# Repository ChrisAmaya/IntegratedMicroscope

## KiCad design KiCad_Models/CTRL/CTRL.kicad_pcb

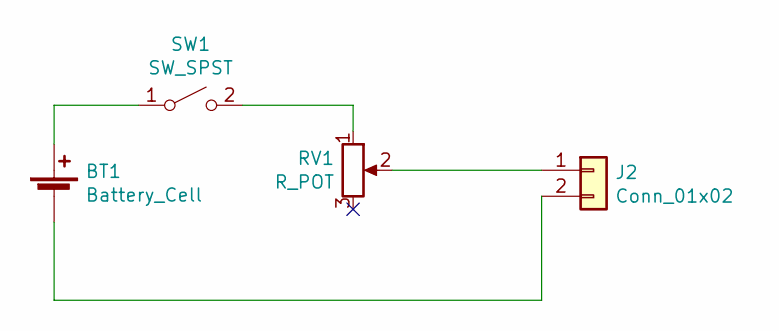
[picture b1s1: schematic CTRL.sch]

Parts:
BT1: Battery_Cell; BatteryHolder_Keystone_1058_1x2032
J2: Conn_01x02; Molex_PicoBlade_53047-0210_1x02_P1.25mm_Vertical
RV1: R_POT; Potentiometer_Bourns_PRS11S_Vertical
SW1: SW_SPST; SW_SPST_EVQPE1

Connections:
unnamed: BT1.1 (+), SW1.1 (A)
unnamed: BT1.2 (-), J2.2
unnamed: J2.1, RV1.2
unnamed: RV1.1, SW1.2 (B)

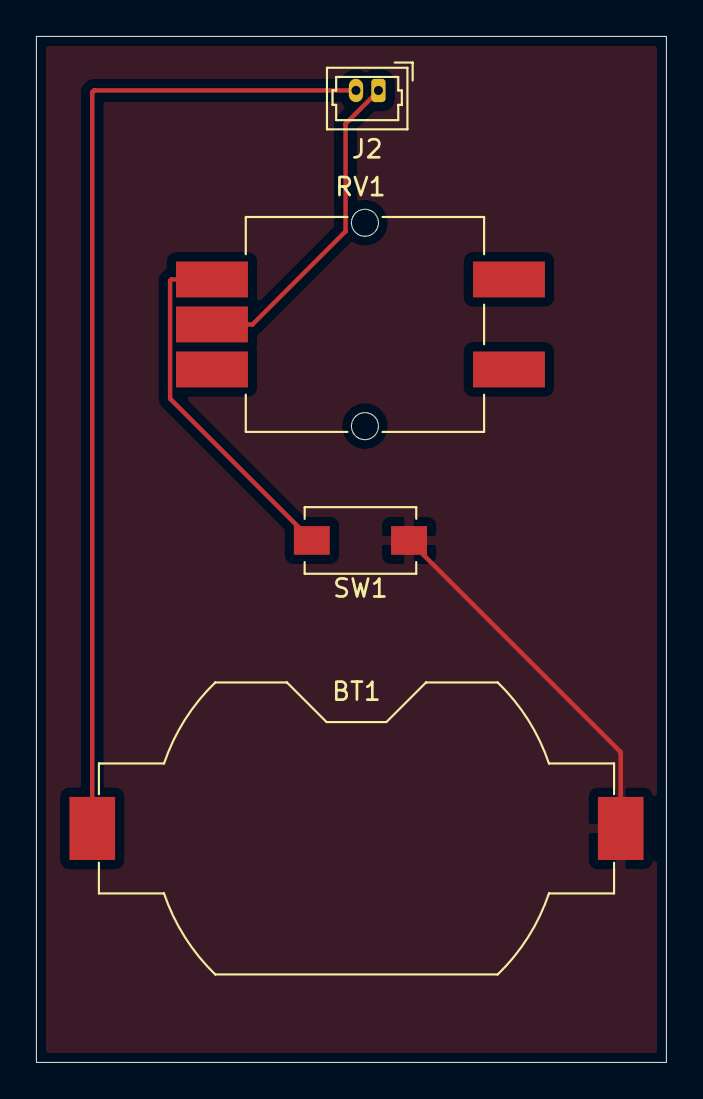
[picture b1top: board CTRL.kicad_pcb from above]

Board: 2 copper layers, 35.0 x 57.0 mm, 4 parts (0 on the bottom side), 4 nets.

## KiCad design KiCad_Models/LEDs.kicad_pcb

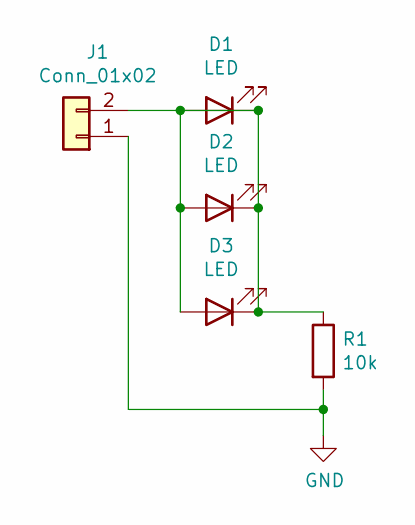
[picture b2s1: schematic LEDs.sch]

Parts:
D1, D2, D3: LED; LED_0805_2012Metric_Pad1.15x1.40mm_HandSolder
J1: Conn_01x02; Molex_PicoBlade_53047-0210_1x02_P1.25mm_Vertical
R1: 10k; R_0201_0603Metric

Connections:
GND: J1.1, R1.2
unnamed: D1.1 (K), D1.2 (A), D2.1 (K), D2.2 (A), D3.1 (K), D3.2 (A), J1.2, R1.1

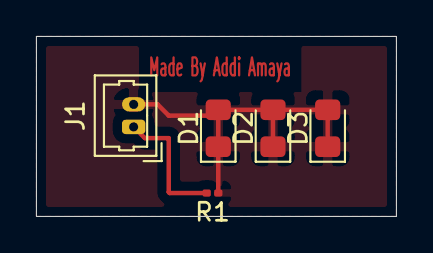
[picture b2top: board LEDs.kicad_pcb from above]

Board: 2 copper layers, 20.0 x 10.0 mm, 5 parts (0 on the bottom side), 2 nets.

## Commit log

2022-05-07 uploaded model into repo
